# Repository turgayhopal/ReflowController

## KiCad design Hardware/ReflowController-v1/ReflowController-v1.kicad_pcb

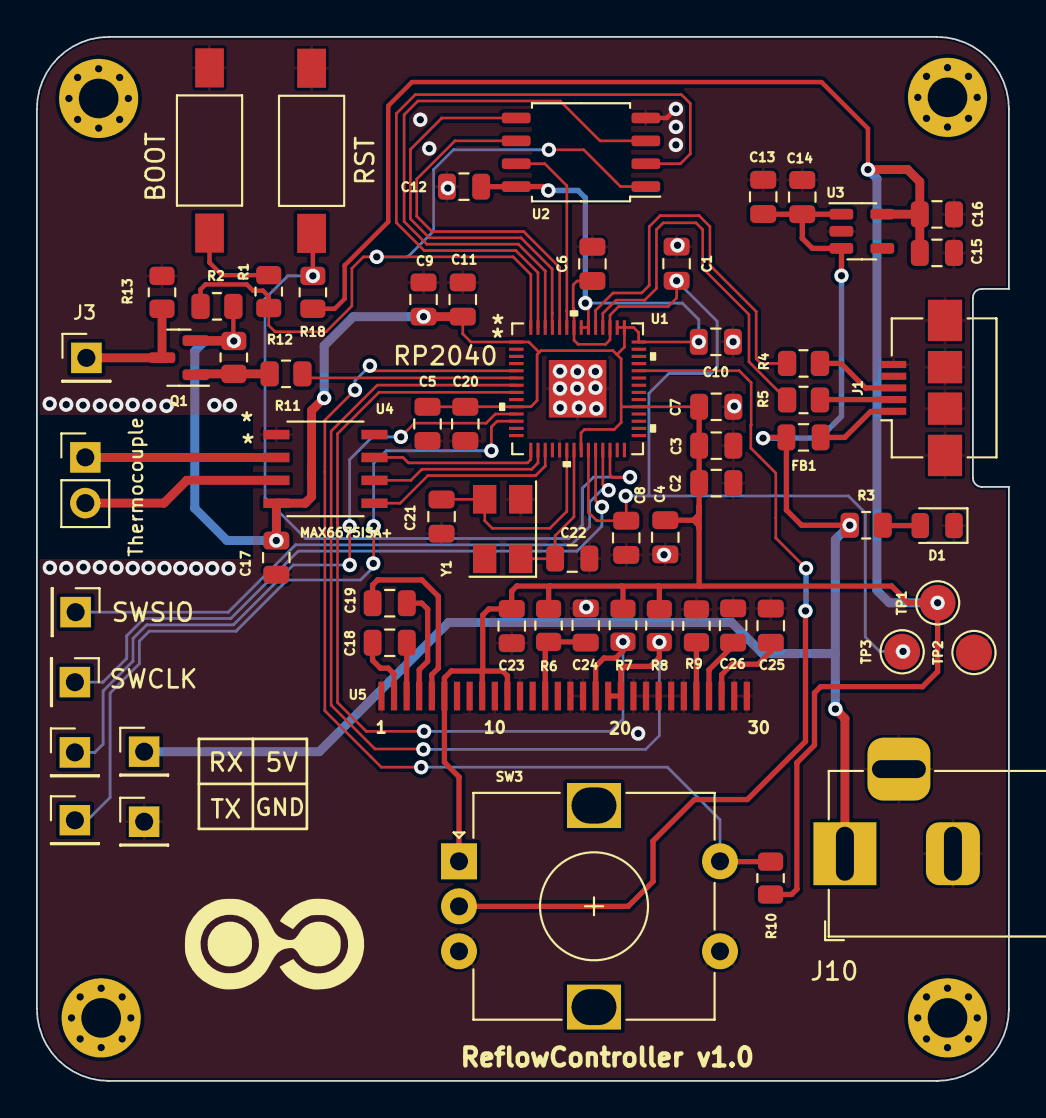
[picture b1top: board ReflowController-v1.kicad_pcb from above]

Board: 2 copper layers, 54.0 x 58.0 mm, 69 parts (0 on the bottom side), 44 nets.

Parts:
5V: Conn_01x01_Male; PinHeader_1x01_P2.54mm_Vertical
BOOT: SW_Push; SW_SPST_FSMSM
C1, C2, C3, C4, C5, C6, C7, C8, C9, C10, C11, C12, C13, C16, C17, C20, C24: 100nF; C_0805_2012Metric
C14, C15, C18, C19, C23: 1uF; C_0805_2012Metric
C21: 22pF; C_0805_2012Metric
C22: 27pF; C_0805_2012Metric
C25, C26: 2.2uF; C_0805_2012Metric
D1: LED; LED_0805_2012Metric
FB1: FerriteBead; C_0805_2012Metric
GND: Conn_01x01_Male; PinHeader_1x01_P2.54mm_Vertical
H1: HOLE-1; MountingHole_2.2mm_M2_Pad_Via
H2: HOLE-2; MountingHole_2.2mm_M2_Pad_Via
H3, H3#2: HOLE-3; MountingHole_2.2mm_M2_Pad_Via
J1: USB_B_Micro; USB_Micro-B_Amphenol_10104110_Horizontal
J3: Conn_01x01_Male; PinHeader_1x01_P2.54mm_Vertical
J10: Barrel_Jack_Switch; BarrelJack_Horizontal
Q1: MMBT3906; SOT-23
R1, R3, R11, R18: 1K; R_0805_2012Metric
R2: DNF; R_0805_2012Metric
R4, R5: 47R; R_0805_2012Metric
R6, R7, R8: 4.7K; R_0805_2012Metric
R9: 390K; R_0805_2012Metric
R10, R12, R13: 10K; R_0805_2012Metric
RST: SW_Push; SW_SPST_FSMSM
RX: Conn_01x01_Male; PinHeader_1x01_P2.54mm_Vertical
SW3: RotaryEncoder_Switch; RotaryEncoder_Alps_EC12E-Switch_Vertical_H20mm
SWCLK: Conn_01x01_Male; PinHeader_1x01_P2.54mm_Vertical
SWSIO: Conn_01x01_Male; PinHeader_1x01_P2.54mm_Vertical
TP1: 3.3V; TestPoint_Pad_D2.0mm
TP2: GND; TestPoint_Pad_D2.0mm
TP3: 1.1V; TestPoint_Pad_D2.0mm
TX: Conn_01x01_Male; PinHeader_1x01_P2.54mm_Vertical
Thermocouple: Conn_01x02_Male; PinHeader_1x02_P2.54mm_Vertical
U1: RP2040
U2: W25Q128JVS; SOIC-8_5.23x5.23mm_P1.27mm
U3: TLV70233_SOT23-5; SOT-23-5
U4: MAX6675ISA+; MAX6675ISA&plus_
U5: UG-2864HSWEG01; 1X30-0.7MM
Y1: 12Mhz; Crystal_SMD_5032-4Pin_5.0x3.2mm

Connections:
1.1V: C1.2, C6.1, C8.1, TP3.1, U1.23 (DVDD), U1.45 (VREG_VOUT), U1.50 (DVDD)
3.3V: C2.2, C3.1, C4.2, C5.1, C7.2, C9.2, C10.2, C11.2, C12.2, C15.1, C16.1, C17.1, C20.2, C23.2, Q1.2 (E), R2.2, R6.1, R7.1, R8.1, R10.1, R12.2, R18.2, SW3.A, TP1.1, U1.1 (IOVDD), U1.10 (IOVDD), U1.22 (IOVDD), U1.33 (IOVDD), U1.42 (IOVDD), U1.43 (ADC_AVDD), U1.44 (VREG_VIN), U1.48 (USB_VDD), U1.49 (IOVDD), U2.8 (VCC), U3.5 (OUT), U4.4 (VCC), U5.6 (VBAT), U5.9 (VDD), U5.11 (BS1)
5V: 5V.1, C13.1, C14.1, FB1.2, J10.1, R3.1, U3.1 (IN), U3.3 (EN)
/RP2040 Sheet/QSPI_SCLK: U1.52 (QSPI_SCLK), U2.6 (CLK)
/RP2040 Sheet/QSPI_SD0: U1.53 (QSPI_SD0), U2.5 (DI(IO0))
/RP2040 Sheet/QSPI_SD1: U1.55 (QSPI_SD1), U2.2 (DO(IO1))
/RP2040 Sheet/QSPI_SD2: U1.54 (QSPI_SD2), U2.3 (IO2)
/RP2040 Sheet/QSPI_SD3: U1.51 (QSPI_SD3), U2.7 (IO3)
/RP2040 Sheet/QSPI_SS: R1.2, R2.1, U1.56 (QSPI_SS_N), U2.1 (~CS)
/RP2040 Sheet/RUN: R18.1, RST.2, U1.26 (RUN)
/RP2040 Sheet/SWCLK: SWCLK.1, U1.24 (SWCLK)
/RP2040 Sheet/SWDIO: SWSIO.1, U1.25 (SWDIO)
/RP2040 Sheet/XIN: C21.2, U1.20 (XIN), Y1.3
/RP2040 Sheet/XOUT: C22.2, U1.21 (XOUT), Y1.1
/Thermocouple Sheet/T+: Thermocouple.2, U4.3 (T+)
/Thermocouple Sheet/T-: Thermocouple.1, U4.2 (T-)
/USB Sheet/D+: J1.3 (D+), R4.1
/USB Sheet/D-: J1.2 (D-), R5.1
ADC0: SW3.C, U1.38 (GPIO26/ADC0)
GND: BOOT.1, C1.1, C2.1, C3.2, C4.1, C5.2, C6.2, C7.1, C8.2, C9.1, C10.1, C11.1, C12.1, C13.2, C14.2, C15.2, C16.2, C17.2, C20.1, C21.1, C22.1, C23.1, C24.1, C25.1, C26.1, D1.1 (K), GND.1, J1.5 (GND), J1.6 (Shield), J10.2, J10.3, R9.2, R13.1, RST.1, SW3.B, SW3.S2, TP2.1, U1.19 (TESTEN), U1.57 (GND), U2.4 (GND), U3.2 (GND), U4.1 (GND), U5.1 (MT), U5.8 (VSS), U5.10 (BS0), U5.12 (BS2), U5.16 (R/W), U5.17 (E/RD), U5.21 (D3), U5.22 (D4), U5.23 (D5), U5.24 (D6), U5.25 (D7), U5.29 (VLSS), U5.30 (MT2), Y1.2
GPIO3: R10.2, SW3.S1, U1.5 (GPIO3)
GPIO4: R11.1, U1.6 (GPIO4)
GPIO5: R8.2, U1.7 (GPIO5), U5.19 (D1/SCLK), U5.20 (D2)
GPIO6: R7.2, U1.8 (GPIO6), U5.18 (D0/DI)
GPIO8: RX.1, U1.11 (GPIO8)
GPIO9: TX.1, U1.12 (GPIO9)
GPIO12: U1.15 (GPIO12), U4.7 (SO)
GPIO13: U1.16 (GPIO13), U4.6 (*CS)
GPIO14: U1.17 (GPIO14), U4.5 (SCK)
unnamed: BOOT.2, R1.1
unnamed: C18.1, U5.3 (C2N)
unnamed: C18.2, U5.2 (C2P)
unnamed: C19.1, U5.4 (C1P)
unnamed: C19.2, U5.5 (C1N)
unnamed: C24.2, R6.2, U5.14 (/RES)
unnamed: C25.2, U5.28 (VCC)
unnamed: C26.2, U5.27 (VCOMH)
unnamed: D1.2 (A), R3.2
unnamed: FB1.1, J1.1 (VBUS)
unnamed: J3.1, Q1.3 (C), R13.2
unnamed: Q1.1 (B), R11.2, R12.1
unnamed: R9.1, U5.26 (IREF)
USB_D+: R4.2, U1.47 (USB_DP)
USB_D-: R5.2, U1.46 (USB_DM)

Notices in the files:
parts and their libraries:
Copyright 2021 Accelerated Designs. All rights reserved.
